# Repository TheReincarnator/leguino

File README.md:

# Disclaimer and warning

The instructions, images, schematics, source codes, etc. may not be accurate nor complete.
Use at your own risk.

LEGO<sup>®</sup> is a trademark of the LEGO Group of companies which does not sponsor, authorize or endorse this site.<br/>
LEGUINO<sup>™</sup> is a trademark of Leguino Ltd., which is independent of this Leguino project.

**Attention**: Please note that there are two projects with the name "Leguino" out there:

1. This open-source, free GitHub project, focussing on the creation of an Arduino shield to drive standard LEGO<sup>®</sup> Technic motors and lights. You can find more details on the history of the project in this readme, and at [Thomas Jacob's website](https://www.thomasjacob.de/kreativ/leguino-en). In this project, you take your existing LEGO<sup>®</sup> Technic models and bring them to life by programming against an Arduino API.

2. A commercial project, started as a Kickstarter campaign, focussing on the creation of proprietary hardware bricks compatible to the geometry of LEGO<sup>®</sup>, with Arduino and Raspberry Pi programming. You can find more details on that project at [Leguino.com](http://leguino.com).

# Introduction

[LEGO<sup>®</sup> Mindstorms](https://www.lego.com/de-de/mindstorms) is a wonderful platform to playfully get used to robotics and programming. Kids can complete their existing LEGO<sup>®</sup> collection with motors and sensors, and the graphical programming environment is easy to understand, but it also contains complex concepts like commands, iterations, branching, variables, and events.

LEGO<sup>®</sup> Mindstorms is, on the other hand, not very cheap (especially for the inquisitive offspring). Though my son already had a rich collection of LEGO<sup>®</sup> Technic models with motors, lights, and switches, it lacks of sensors and even programming.

But he was very much interested in that stuff.

So I thought, let's try to fill the gap and build an open-source platform based on LEGO<sup>®</sup> Technic, that is cheap enough (goal <100€) and also easy to understand. To do so, [Arduino](https://www.arduino.cc/) is the perfect choice, for the following reasons:

* An Arduino Nano costs less than 20€, sometimes even below 10€.
* You can power it with a regular LEGO<sup>®</sup> Technic battery.
* It starts up in less than a second (in contrast to the [Raspberry Pi](https://www.raspberrypi.org/) for instance), a circumstance that is important when building models with a switchable battery.
* It has enough inputs/outputs for about 10 devices.

I added a programming platform, an API that abstracts from sensors, actors, control sequences etc., so the offspring (and you) can focus on the actual project.

If you want to learn more about how Leguino was invented, [visit my web site](http://www.thomasjacob.de/kreativ/leguino-en).

# Getting started

Leguino is both a custom Arduino shield and wiring, as well as a library for Arduino. To get started, you need to build the shield yourself (sorry, no orderable ready-made PCB as of today), and then install the Arduino IDE, and the Leguino library.

## Hardware

First of all, you require an Arduino Uno or Nano. I recommend the latter, as it fulfills the Leguino requirements and it has much smaller dimensions.

As there is no Leguino PCB design as of today (maybe you'd like to contribute?), you need to buy an Arduino shield and all electronics parts, and solder them manually.

You also need to make LEGO<sup>®</sup> Technic wires and the case.

You can find all parts in the [parts list](docs/parts.md), as well as wiring and board schematics in [schematics folder](docs/schematics). I also took [some pictures](docs/photos) while building the prototype. Maybe my [my web site](http://www.thomasjacob.de/kreativ/leguino-en) helps, too.

## Software

To write your own Leguino program, you first need the Arduino IDE, which you can [download here].

After installation, take this Leguino source folder, and put it into the libraries folder of your installation.

Then, start your programs by using one of the example sketches found in [examples)(examples), and read the API of the [Leguino core](core/LeguinoCore.h), [its actors](actor/Actor.h), and [its sensors](sensor/Sensor.h).

There is also a kids-friendly (but German) documentation available, [see here](docs/Leguino-Kurzanleitung-DE.doc).

# Contribute

Do you have suggestions, ideas, even code or PCB designs? Please contact me at http://thomasjacob.de/footer/contact.

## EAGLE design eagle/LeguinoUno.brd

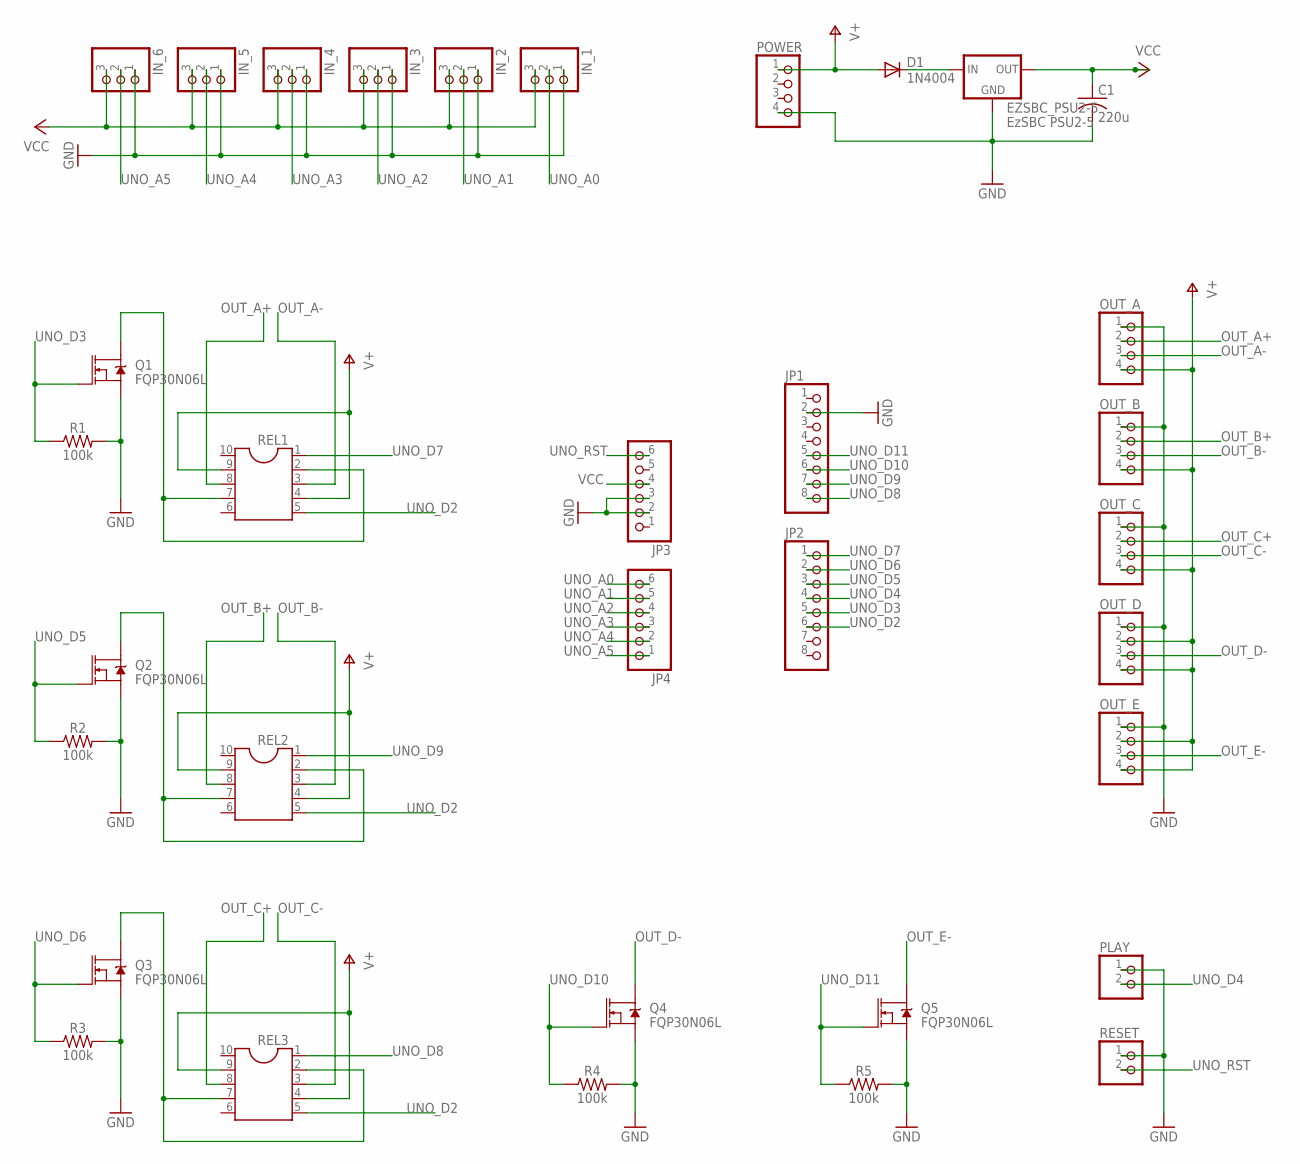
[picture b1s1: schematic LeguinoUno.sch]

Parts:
C1: 220u; C050-030X075
D1: 1N4004; DO41-10
EZSBC_PSU2-5: EzSBC PSU2-5; TO-220-ALT
IN_1, IN_2, IN_3, IN_4, IN_5, IN_6: PINHD-1X3; 1X03
JP1, JP2: PINHD-1X8; 1X08
JP3, JP4: PINHD-1X6; 1X06
OUT_A: PINHD-1X4; 1X04
OUT_B: PINHD-1X4; 1X04
OUT_C: PINHD-1X4; 1X04
OUT_D: PINHD-1X4; 1X04
OUT_E: PINHD-1X4; 1X04
PLAY: PINHD-1X2; 1X02
POWER: PINHD-1X4; 1X04
Q1, Q2, Q3, Q4, Q5: FQP30N06L; TO220V
R1, R2, R3, R4, R5: 100k; AXIAL-0.3
REL1, REL2, REL3: DIL10
RESET: PINHD-1X2; 1X02

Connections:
GND: C1.2, EZSBC_PSU2-5.GND, IN_1.1, IN_2.1, IN_3.1, IN_4.1, IN_5.1, IN_6.1, JP1.2, JP3.2, JP3.3, OUT_A.1, OUT_B.1, OUT_C.1, OUT_D.1, OUT_E.1, PLAY.1, POWER.4, Q1.3 (S), Q2.3 (S), Q3.3 (S), Q4.3 (S), Q5.3 (S), R1.P$2 (2), R2.P$2 (2), R3.P$2 (2), R4.P$2 (2), R5.P$2 (2), RESET.1
unnamed: D1.C, EZSBC_PSU2-5.IN
unnamed: Q1.2 (D), REL1.2, REL1.7
unnamed: Q2.2 (D), REL2.2, REL2.7
unnamed: Q3.2 (D), REL3.2, REL3.7
OUT_A+: OUT_A.2, REL1.8
OUT_A-: OUT_A.3, REL1.3
OUT_B+: OUT_B.2, REL2.8
OUT_B-: OUT_B.3, REL2.3
OUT_C+: OUT_C.2, REL3.8
OUT_C-: OUT_C.3, REL3.3
OUT_D-: OUT_D.3, Q4.2 (D)
OUT_E-: OUT_E.3, Q5.2 (D)
UNO_A0: IN_1.2, JP4.6
UNO_A1: IN_2.2, JP4.5
UNO_A2: IN_3.2, JP4.4
UNO_A3: IN_4.2, JP4.3
UNO_A4: IN_5.2, JP4.2
UNO_A5: IN_6.2, JP4.1
UNO_D2: JP2.6, REL1.5, REL2.5, REL3.5
UNO_D3: JP2.5, Q1.1 (G), R1.P$1 (1)
UNO_D4: JP2.4, PLAY.2
UNO_D5: JP2.3, Q2.1 (G), R2.P$1 (1)
UNO_D6: JP2.2, Q3.1 (G), R3.P$1 (1)
UNO_D7: JP2.1, REL1.1
UNO_D8: JP1.8, REL3.1
UNO_D9: JP1.7, REL2.1
UNO_D10: JP1.6, Q4.1 (G), R4.P$1 (1)
UNO_D11: JP1.5, Q5.1 (G), R5.P$1 (1)
UNO_RST: JP3.6, RESET.2
V+: D1.A, OUT_A.4, OUT_B.4, OUT_C.4, OUT_D.2, OUT_D.4, OUT_E.2, OUT_E.4, POWER.1, REL1.4, REL1.9, REL2.4, REL2.9, REL3.4, REL3.9
VCC: C1.1, EZSBC_PSU2-5.OUT, IN_1.3, IN_2.3, IN_3.3, IN_4.3, IN_5.3, IN_6.3, JP3.4

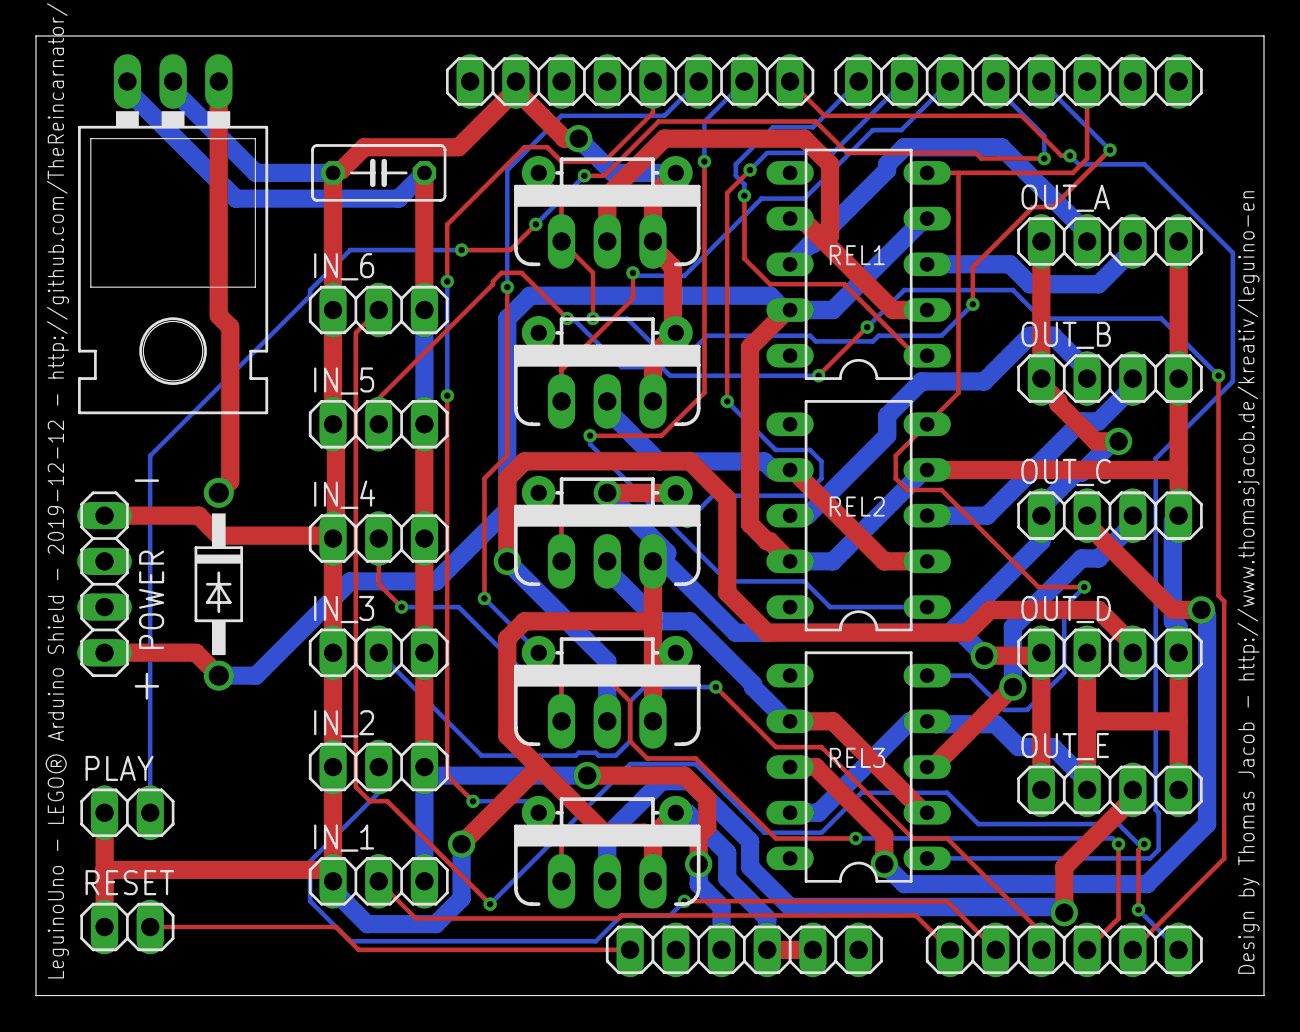
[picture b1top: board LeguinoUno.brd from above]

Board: 2 copper layers, 68.2 x 53.3 mm, 34 parts (0 on the bottom side), 32 nets.

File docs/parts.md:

# Electronic parts

## Leguino shield prototype

* Prototype Shield
* Header Pin set
* 5x 100k resistor
* 3x bistable Print relay TQ2L25, 1A, 2x switch UK Panasonic bistable 5V 2x switch, 1A 110V DC (125V AV) 30W (62,5 VA) ([Conrad #505062](http://www.conrad.de/ce/de/product/505062))
* 5x FQP30N06L MOSFET N-Channel
* Switching regulator, output 5V/1A, input 9V (e.g. [EzSBC PSU2-5](https://www.ezsbc.com/index.php/psu2-5.html) or [Conrad #167805, W78-5V0](http://www.conrad.de/ce/de/product/167805))
* Diode 1N4001 ([Conrad #162213](http://www.conrad.de/ce/de/product/162213))
* Play button MS-402/SW
* Reset button MS-402/RT
* 2x Black female railroad plug ([Conrad #731927](http://www.conrad.de/ce/de/product/731927))
* 2x Red female railroad plug ([Conrad #731919](http://www.conrad.de/ce/de/product/731919))
* 6x Yellow female railroad plug ([Conrad #731935](http://www.conrad.de/ce/de/product/731935))
* Several black male railroad plugs ([Conrad #730572](http://www.conrad.de/ce/de/product/730572))
* Several red male railroad plugs ([Conrad #730564](http://www.conrad.de/ce/de/product/730564))
* Several yellow male railroad plugs ([Conrad #730580](http://www.conrad.de/ce/de/product/730580))

## Sensors

* Proximity (distance) sensor ([Conrad #504591](http://www.conrad.de/ce/de/product/504591) or [Reichelt #GP2-1080](http://www.reichelt.de/Sensoren/GP2-1080/3/index.html?&ACTIO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

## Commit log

2015-12-27 Initial check-in.
2015-12-27 Ignore file.
2016-10-28 Refactored Leguino API entirely (merged inputs/outputs and actors/sensors into one concept, providing a better API)
2017-08-12 Docs, schematics, and photos.
2017-12-29 docs: add API documentation, improve and translate example
2017-12-29 docs: add code of conduct and license
2017-12-29 docs: introduction and readme
2017-12-31 docs: add eagle schematics and first board version
2018-02-07 Continued EAGLE schematic and board for Arduino Uno.
2018-04-11 docs: reference to leguino.com
2018-04-19 Added LEGUINO trademark note.
2018-04-23 Updated EAGLE schematics and board, moved EAGLE files to top-level, created Gerber files.
2018-05-29 fix VCC Arduino connection and width, reroute
2018-05-29 docs: update parts list
2019-12-12 fix analog pin assignment for Uno
2019-12-12 tester project
2020-01-12 pretty print code
2020-01-12 update Gerber files after pin assignment correction

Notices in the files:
parts and their libraries:
SparkFun-DiscreteSemi: Licensing: Creative Commons ShareAlike 4.0 International - https://creativecommons.org/licenses/by-sa/4.0
